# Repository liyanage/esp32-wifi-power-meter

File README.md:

# ESP32 WiFi voltage meter

This is a simple voltage meter that can be powered from about 5 to 24v
and queried via WiFi.

## PCB

## Software

## Usage

The software implements a configuration menu that you can enter during boot. It's used
to set up WiFi credentials and ADC voltage calibration.

### WiFi Configuration

### ADC Voltage Calibration

Drop into ADC calibration menu at boot:

    [...]
    Press any key within the next 2 seconds to enter configuration mode
    Press any key within the next 1 seconds to enter configuration mode
    Key press detected
    Entering configuration mode

    Choose a setting to change:
    w - WiFi settings
    i - IP address settings
    c - ADC voltage measurement calibration
    r - Reboot
    > c

    Raw ADC value: 0.217, calibrated value: 9.438, y-intercept: 1.358, slope: 37.318
    Choose an option:
    i - change calibration y-intercept
    s - change calibration slope
    n - Commit current values to non-volatile storage
    c - cancel

Determine calibration y-intercept and slope values:

* Set input voltage to 5v, hit the return key a few times, note the ADC raw value, e.g. 0.097
* Set input voltage to 24v, hit the return key a few times, note the raw value, e.g. 0.607
* Slope = delta_voltage/delta_adc = (24-5)/(0.607-0.097) = 37.2549
* Y-intercept = voltage - adc * slope = 24-0.607*37.2549 = 1.3863

Set those values using the menu options and hit return a few times to check.
Change the voltage and check again.

Commit the values to non-volatile storage with the corresponding menu command.

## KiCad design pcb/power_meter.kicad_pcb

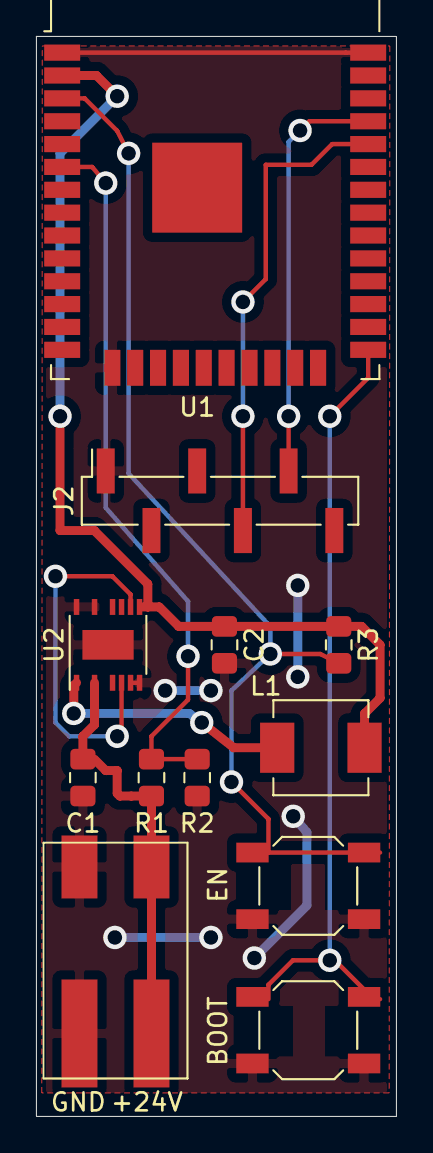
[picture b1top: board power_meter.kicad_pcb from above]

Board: 2 copper layers, 20.0 x 60.0 mm, 12 parts (0 on the bottom side), 10 nets.

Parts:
C1: 4.7uF; C_0805_2012Metric_Pad1.15x1.40mm_HandSolder
C2: 350uF; C_0805_2012Metric_Pad1.15x1.40mm_HandSolder
J1: WAGO_2060-451_998-404
J2: Conn_01x06; PinHeader_1x06_P2.54mm_Vertical_SMD_Pin1Right
L1: 10uH; L_Vishay_IHLP-2020
R1: 1M; R_0805_2012Metric_Pad1.15x1.40mm_HandSolder
R2: 100k; R_0805_2012Metric_Pad1.15x1.40mm_HandSolder
R3: 10k; R_0805_2012Metric_Pad1.15x1.40mm_HandSolder
SW1: EN; SW_SPST_SKQG_WithStem
SW2: BOOT; SW_SPST_SKQG_WithStem
U1: ESP32-WROOM-32
U2: LTC3630MSE; Linear_MSOP-12-16-1EP_3x4mm_P0.5mm

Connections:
+24V: C1.1, J1.2, R1.1, U2.3
/Vout: C2.1, L1.2, R3.1, U1.2, U2.9
GND: C1.2, C2.2, J1.1, J2.1, R2.2, SW1.1, SW2.1, U1.1, U1.15, U1.38, U2.7, U2.8, U2.14, U2.16, U2.17
unnamed: J2.4, U1.34
unnamed: J2.5, U1.35
unnamed: L1.1, U2.1
unnamed: R1.2, R2.1, U1.6
unnamed: R3.2, SW1.2, U1.3
unnamed: SW2.2, U1.25
unnamed: U2.6, U2.10

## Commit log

2019-06-10 init
2019-06-10 Cleanup
2019-06-12 Add ADC calibration config submenu
2019-06-12 Add ADC calibration config menu
2019-07-23 Add photo, fix up paths
2019-11-16 Start using reset of the board via RTS/DTR signals
